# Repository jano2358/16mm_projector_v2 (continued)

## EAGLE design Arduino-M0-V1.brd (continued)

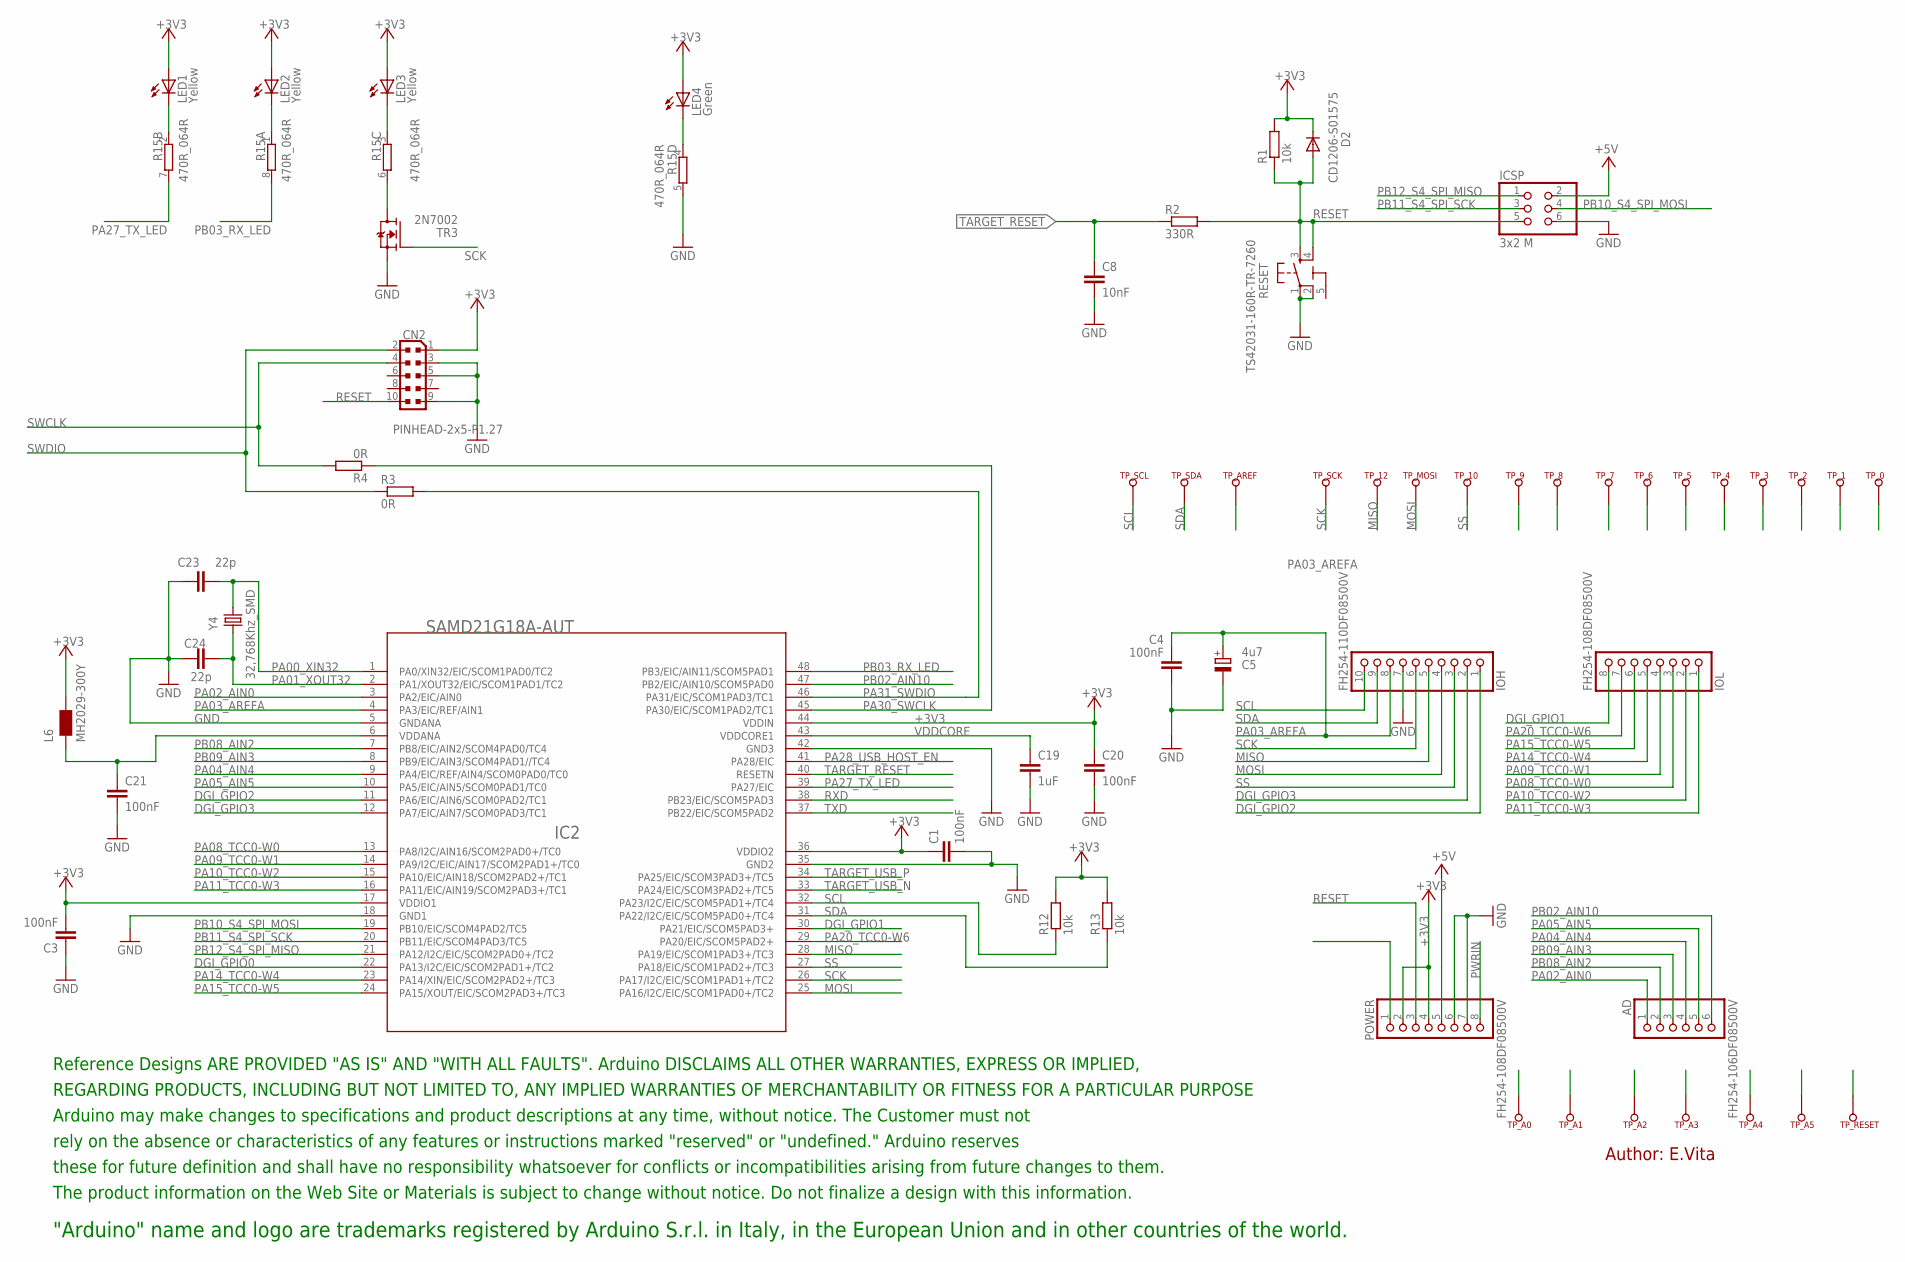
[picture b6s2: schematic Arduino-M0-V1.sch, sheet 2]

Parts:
AD: FH254-106DF08500V; 1X06
C1, C3, C4, C20, C21: 100nF; C0603-ROUND
C5: 4u7; SMC_A
C8: 10nF; C0603-ROUND
C19: 1uF; C0603-ROUND
C23, C24: 22p; C0603-ROUND
CN2: PINHEAD-2x5-P1.27; PINHEAD_2X05_127
D2: CD1206-S01575; MINIMELF
IC2: SAMD21G18A-AUT; TQFP48-7X7
ICSP: 3x2 M; 2X03
IOH: FH254-110DF08500V; 1X10
IOL: FH254-108DF08500V; 1X08
L6: MH2029-300Y; 0805
LED1, LED2, LED3: Yellow; CHIPLED_0805
LED4: Green; CHIPLED_0805
POWER: FH254-108DF08500V; 1X08
R1, R12, R13: 10k; R0603-ROUND
R2: 330R; R0603-ROUND
R3, R4: 0R; R0603-ROUND
R15: 470R_064R; CAY16
RESET: TS42031-160R-TR-7260; TS42
TP_0, TP_1, TP_2, TP_3, TP_4, TP_5, TP_6, TP_7, TP_8, TP_9, TP_10, TP_12: TP_SP; TP-SP
TP_A0, TP_A1, TP_A2, TP_A3, TP_A4, TP_A5: TP_SP; TP-SP
TP_AREF: TP_SP; TP-SP
TP_MOSI: TP_SP; TP-SP
TP_RESET: TP_SP; TP-SP
TP_SCK: TP_SP; TP-SP
TP_SCL: TP_SP; TP-SP
TP_SDA: TP_SP; TP-SP
TR3: 2N7002; SOT-23
U$2: DISCLAIMER-SMALL; DISCLAIMER
Y4: 32,768Khz_SMD; RESONATOR_EPSON_FC_145

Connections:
5-GND: RESET.5 (5-GND)
+3V3: C1.1, C3.2, C20.1, CN2.1, D2.C, IC2.17 (VDDIO1), IC2.36 (VDDIO2), IC2.44 (VDDIN), L6.2, LED1.A, LED2.A, LED3.A, LED4.A, POWER.2, POWER.4, R1.2, R12.2, R13.2; also elsewhere on the board
+5V: ICSP.2, POWER.5; also elsewhere on the board
DGI_GPIO0: IC2.22 (PA13/I2C/EIC/SCOM2PAD1+/TC2)
DGI_GPIO1: IC2.30 (PA21/EIC/SCOM5PAD3+), IOL.8, TP_7.X
DGI_GPIO2: IC2.11 (PA6/EIC/AIN6/SCOM0PAD2/TC1), IOH.1, TP_8.X
DGI_GPIO3: IC2.12 (PA7/EIC/AIN7/SCOM0PAD3/TC1), IOH.2, TP_9.X
GND: C1.2, C3.1, C4.2, C5.-, C8.2, C19.2, C20.2, C21.2, C23.1, C24.1, CN2.3, CN2.5, CN2.9, IC2.5 (GNDANA), IC2.18 (GND1), IC2.35 (GND2), IC2.42 (GND3), ICSP.6, IOH.7, POWER.6, POWER.7, R15.5 (2), RESET.1, RESET.2, TR3.2 (S); also elsewhere on the board
MISO: IC2.28 (PA19/EIC/SCOM1PAD3+/TC3), IOH.5, TP_12.X
MOSI: IC2.25 (PA16/I2C/EIC/SCOM1PAD0+/TC2), IOH.4, TP_MOSI.X
unnamed: LED1.C, R15.2 (1)
unnamed: LED2.C, R15.1
unnamed: LED3.C, R15.3 (1)
unnamed: LED4.C, R15.4 (1)
unnamed: R15.6 (2), TR3.1 (D)
unnamed: C21.1, IC2.6 (VDDANA), L6.1
PA00_XIN32: C23.2, IC2.1 (PA0/XIN32/EIC/SCOM1PAD0/TC2), Y4.P$2 (2)
PA01_XOUT32: C24.2, IC2.2 (PA1/XOUT32/EIC/SCOM1PAD1/TC2), Y4.P$1 (1)
PA02_AIN0: AD.1, IC2.3 (PA2/EIC/AIN0), TP_A0.X
PA03_AREFA: C4.1, C5.+, IC2.4 (PA3/EIC/REF/AIN1), IOH.8, TP_AREF.X
PA04_AIN4: AD.4, IC2.9 (PA4/EIC/REF/AIN4/SCOM0PAD0/TC0), TP_A3.X
PA05_AIN5: AD.5, IC2.10 (PA5/EIC/AIN5/SCOM0PAD1/TC0), TP_A4.X
PA08_TCC0-W0: IC2.13 (PA8/I2C/AIN16/SCOM2PAD0+/TC0), IOL.3, TP_2.X
PA09_TCC0-W1: IC2.14 (PA9/I2C/EIC/AIN17/SCOM2PAD1+/TC0), IOL.4, TP_3.X
PA10_TCC0-W2: IC2.15 (PA10/EIC/AIN18/SCOM2PAD2+/TC1), IOL.2, TP_1.X
PA11_TCC0-W3: IC2.16 (PA11/EIC/AIN19/SCOM2PAD3+/TC1), IOL.1, TP_0.X
PA14_TCC0-W4: IC2.23 (PA14/XIN/EIC/SCOM2PAD2+/TC3), IOL.5, TP_4.X
PA15_TCC0-W5: IC2.24 (PA15/XOUT/EIC/SCOM2PAD3+/TC3), IOL.6, TP_5.X
PA20_TCC0-W6: IC2.29 (PA20/EIC/SCOM5PAD2+), IOL.7, TP_6.X
PA27_TX_LED: IC2.39 (PA27/EIC), R15.7 (2)
PA28_USB_HOST_EN: IC2.41 (PA28/EIC); also elsewhere on the board
PA30_SWCLK: IC2.45 (PA30/EIC/SCOM1PAD2/TC1), R4.1
PA31_SWDIO: IC2.46 (PA31/EIC/SCOM1PAD3/TC1), R3.2
PB02_AIN10: AD.6, IC2.47 (PB2/EIC/AIN10/SCOM5PAD0), TP_A5.X
PB03_RX_LED: IC2.48 (PB3/EIC/AIN11/SCOM5PAD1), R15.8 (2)
PB08_AIN2: AD.2, IC2.7 (PB8/EIC/AIN2/SCOM4PAD0/TC4), TP_A1.X
PB09_AIN3: AD.3, IC2.8 (PB9/EIC/AIN3/SCOM4PAD1//TC4), TP_A2.X
PB10_S4_SPI_MOSI: IC2.19 (PB10/EIC/SCOM4PAD2/TC5), ICSP.4
PB11_S4_SPI_SCK: IC2.20 (PB11/EIC/SCOM4PAD3/TC5), ICSP.3
PB12_S4_SPI_MISO: IC2.21 (PA12/I2C/EIC/SCOM2PAD0+/TC2), ICSP.1
PWRIN: POWER.8; also elsewhere on the board
RESET: CN2.10, D2.A, ICSP.5, POWER.3, R1.1, R2.2, RESET.3, RESET.4, TP_RESET.X
RXD: IC2.38 (PB23/EIC/SCOM5PAD3)
SCK: IC2.26 (PA17/I2C/EIC/SCOM1PAD1+/TC2), IOH.6, TP_SCK.X, TR3.3 (G)
SCL: IC2.32 (PA23/I2C/EIC/SCOM5PAD1+/TC4), IOH.10, R12.1, TP_SCL.X
SDA: IC2.31 (PA22/I2C/EIC/SCOM5PAD0+/TC4), IOH.9, R13.1, TP_SDA.X
SS: IC2.27 (PA18/EIC/SCOM1PAD2+/TC3), IOH.3, TP_10.X
SWCLK: CN2.4, R4.2
SWDIO: CN2.2, R3.1
TARGET_RESET: C8.1, IC2.40 (RESETN), R2.1
TARGET_USB_N: IC2.33 (PA24/EIC/SCOM3PAD2+/TC5); also elsewhere on the board
TARGET_USB_P: IC2.34 (PA25/EIC/SCOM3PAD3+/TC5); also elsewhere on the board
TXD: IC2.37 (PB22/EIC/SCOM5PAD2)
VDDCORE: C19.1, IC2.43 (VDDCORE1)

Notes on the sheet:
Author: E.Vita

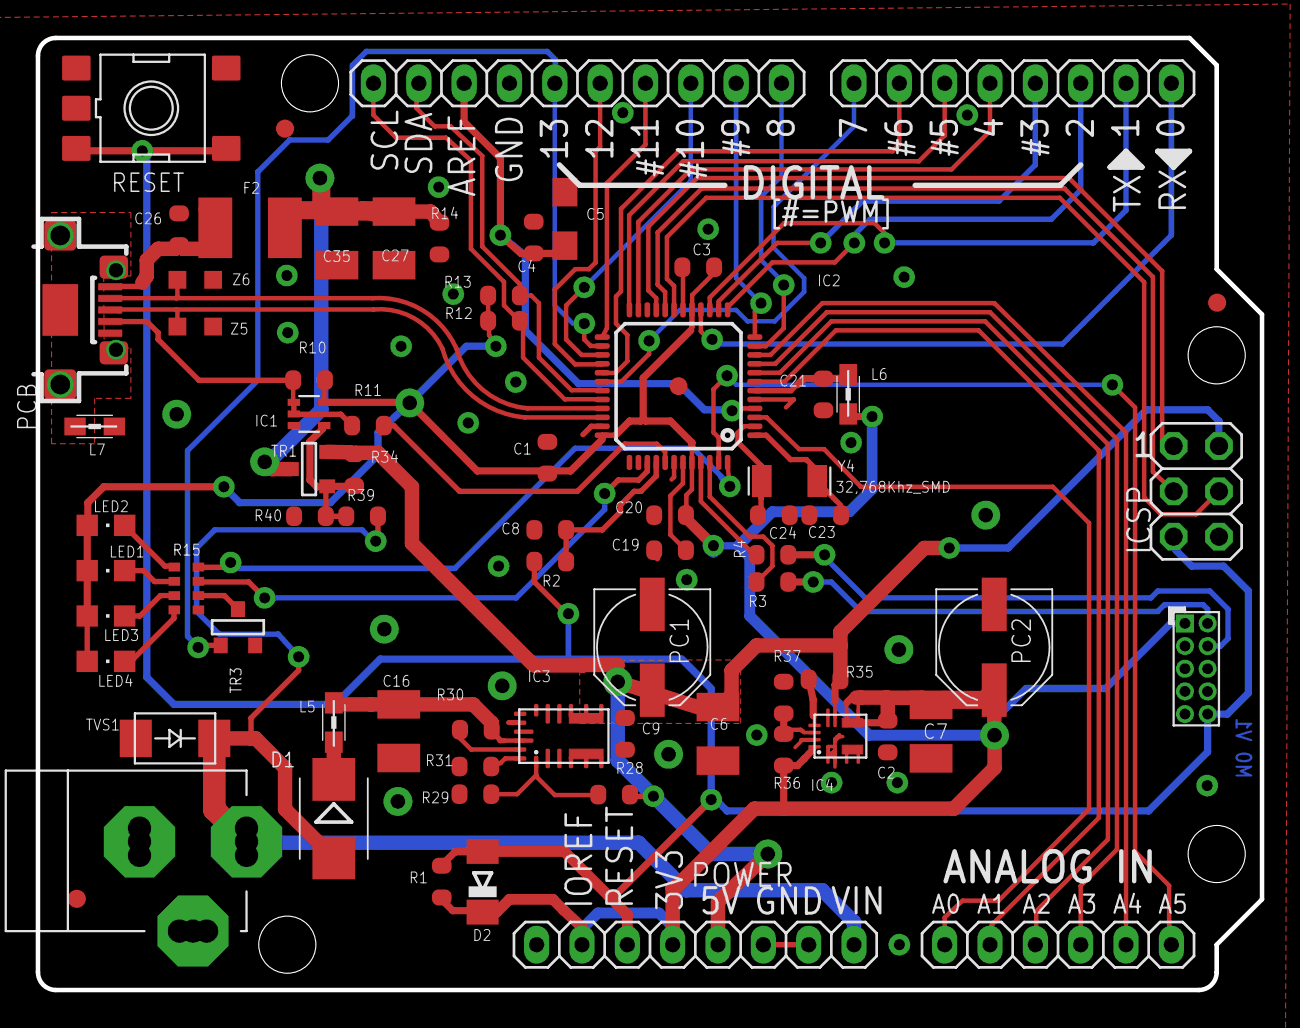
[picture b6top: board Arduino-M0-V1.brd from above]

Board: 4 copper layers, 68.6 x 53.3 mm, 101 parts (0 on the bottom side), 62 nets.

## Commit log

2016-08-12 updated photos, added video
2016-08-14 Update link_to_video
